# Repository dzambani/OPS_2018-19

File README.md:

# OPS
A series of projects for the OPS program by IEEE at UCLA. 
Projects include:

BlinkingLights:
A classic beginner project. The title says it all.

BlinkingLedPot:
A potentiometer controls the rate at which the LED blinks.

IRSensor:
As two IR sensors get closer or farther from each other, an LED will get brighter or dimmer. 

RedLightGreenLight:
A game where we programmed in one arduino for a red or green light to randomly light up, wait for a response (a corresponding button press) by wireless serial communication from another arduino, and repeat the pattern until the player pressing the buttons loses.

Rat:
The capstone project where we built (in teams) a gyroscope controlled rat-bot to race through a maze using two arduinos, radios, and servoes.

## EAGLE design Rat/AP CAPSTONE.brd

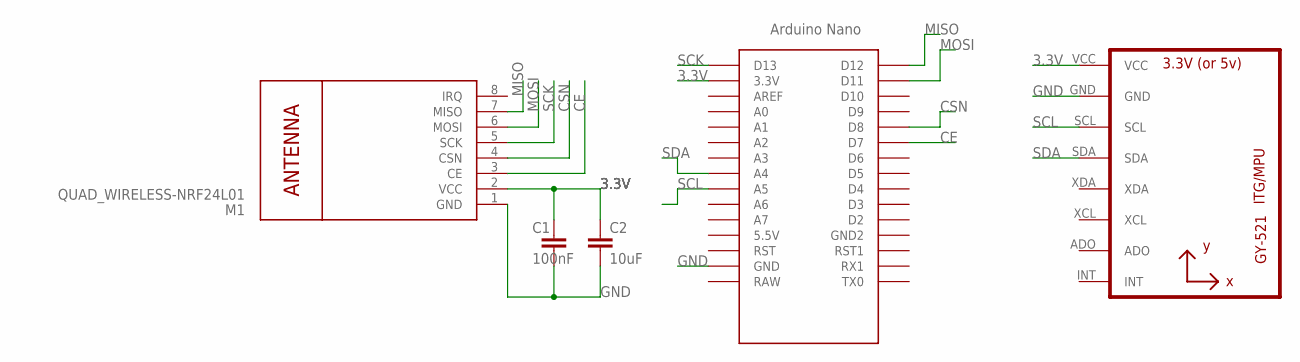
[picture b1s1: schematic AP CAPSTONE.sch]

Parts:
C1: 100nF; RCL_C1206
C2: 10uF; RCL_C1206
M1: QUAD_WIRELESS-NRF24L01
U1: QUAD_GY-521MPU6050; QUAD_GY-521
U$1: ARDUINO-CLONE_NANO

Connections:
3.3V: C1.1, C2.1, M1.2 (VCC), U1.VCC, U$1.3.3V
CE: M1.3 (CE), U$1.D7
CSN: M1.4 (CSN), U$1.D8
GND: C1.2, C2.2, M1.1 (GND), U1.GND, U$1.GND
MISO: M1.7 (MISO), U$1.D12
MOSI: M1.6 (MOSI), U$1.D11
SCK: M1.5 (SCK), U$1.D13
SCL: U1.SCL, U$1.A5
SDA: U1.SDA, U$1.A4

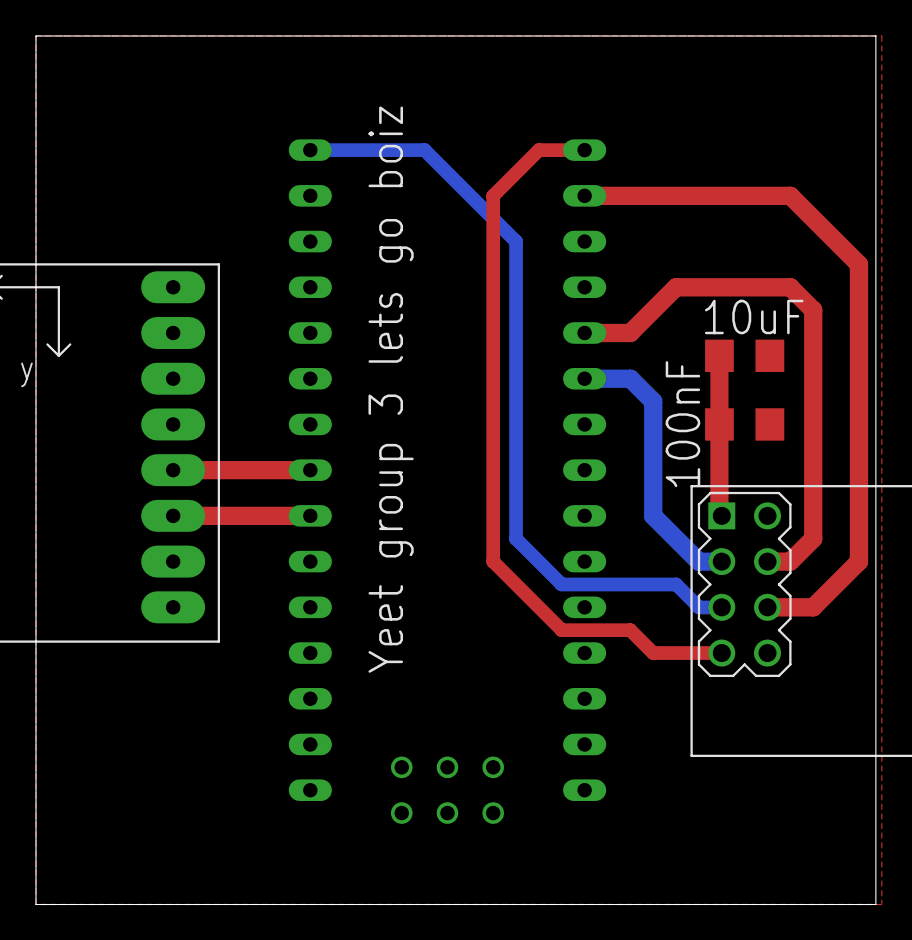
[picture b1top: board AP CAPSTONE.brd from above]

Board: 2 copper layers, 46.7 x 48.2 mm, 5 parts (0 on the bottom side), 9 nets.

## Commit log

2019-09-18 moved from local machine to repo
